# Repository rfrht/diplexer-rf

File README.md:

# Zamin ABL1000 40m Absorptive Diplexer (Rev. A)

> A high-power, 40m (7 MHz) absorptive diplexer designed to clean the output of a Zamin ABL1000 solid-state amplifier and safely dissipate destructive out-of-band harmonics.

## 📌 Project Objective
The Zamin ABL1000 utilizes four M25C24 bipolar transistors in a push-pull configuration. When driven to its absolute 600W limit, it operates deep into saturation, effectively acting as a square-wave generator rich in **odd-order harmonics** (especially the 3rd harmonic at 21 MHz). 

Standard low-pass filters reflect these harmonics back into the amplifier finals, causing extreme thermal stress and potential failure. This **absorptive diplexer** solves the problem by passing the clean 7 MHz fundamental frequency to the antenna while routing the destructive 14 MHz, 21 MHz, and 28 MHz+ harmonics into a dedicated 50-Ohm dummy load.

## 📐 Filter Topology & Specifications
* **Architecture:** 7.5 MHz Crossover, 3-Pole Butterworth Contiguous Diplexer.
* **System Impedance:** 50 Ohms constant (ensuring a flat 1.0:1 SWR presented to the amplifier across the spectrum).
* **Schematic:** [Check here](https://github.com/rfrht/diplexer-rf/blob/main/Others/lpf-40-sch.png).

### Branch Values
| Branch | Port | Component | Target Value | Actual Assembly Value |
| :--- | :--- | :--- | :--- | :--- |
| **Low-Pass** | Antenna | L1 (Series) | 1.06 µH | 1.06 µH |
| **Low-Pass** | Antenna | C1 (Shunt) | 848 pF | 840 pF |
| **Low-Pass** | Antenna | L2 (Series) | 1.06 µH | 1.06 µH |
| **High-Pass** | Dummy Load | C2 (Series) | 424 pF | 420 pF |
| **High-Pass** | Dummy Load | L3 (Shunt) | 0.53 µH | 0.53 µH |
| **High-Pass** | Dummy Load | C3 (Series) | 424 pF | 420 pF |

---

## 🛠️ Hardware & Components

### 1. Capacitor Banks (1260V Series-Parallel Matrix)
To handle 500V+ RF peaks and distribute heat, standard **Yageo 1206 630V C0G ceramic capacitors** are arranged in a 2x4 matrix (2 in series, 4 parallel rows).
* **C1 Bank (840 pF):** Three rows of 470 pF + One row of 270 pF.
* **C2 & C3 Banks (420 pF):** Three rows of 220 pF + One row of 180 pF.

### 2. High-Power Air Core Inductors
* **Material:** 12 AWG bare/enameled copper wire wound on a 1-inch (25.4 mm) form.
* **L1 & L2:** ~9 turns, spaced to ~3.6 cm in length.
* **L3:** ~6 turns, spaced to ~2.54 cm in length.
* **Orthogonal Placement:** L1 is mounted horizontally (X-axis), L2 is horizontal (Y-axis), and L3 is mounted **vertically** (Z-axis). This strict 90-degree geometry guarantees zero magnetic cross-coupling.

### 3. Ports & Dummy Load
* **Main RF Ports (Input & Antenna):** High-temperature, 2,500W-rated **RG-400 Teflon coax pigtails**, soldered directly to the board and terminating in SO-239 connectors to decouple mechanical torque from the FR4 pads.
* **Dummy Load Port:** Edge-mounted PTFE SMA connector feeding a flexible RG-316 jumper.
* **DIY Dummy Load (200W):** Two parallel Ohmite TGHD SOT-227 100-Ohm thick-film resistors (yielding a 50-Ohm load) bolted to a large heatsink with thermal paste, bridged with flat copper strap to eliminate parasitic inductance.

---

## 📏 PCB Layout & RF Design Rules

[The board](https://github.com/rfrht/diplexer-rf/blob/main/Others/lpf-40.png) is a 10x10 cm, 1 oz FR4 prototype with strict RF rules applied:

* **Trace Architecture:** The main LPF signal path uses heavy **6 mm wide traces**, mirrored identically on the top and bottom layers to act as a 2 oz equivalent.
* **Via Stitching:** Top and bottom traces are tied together using vias spaced precisely every **5 mm along the trace borders** to combat the skin effect and create a highly efficient thermal superhighway. 
* **Ground Plane:** Solid copper pours on top and bottom, featuring a 5 mm checkered/staggered via grid. Dense via clusters are placed immediately at the ground pads of C1, L3, and the coax shields. Isolation gaps are set to 3-5 mm to prevent 500V+ arc-overs.
* **Solder Mask Management:**
  * *Removed* (`tStop`/`bStop`) along the main 6 mm LPF path to allow for heavy "solder river" tinning to handle 6A+ RF peaks.
  * *Retained* on the 2 mm traces between the series SMD capacitors to act as a solder dam during assembly.
* **Magnetic Keep-Out Zones:** Ground pours are **completely removed** (`tRestrict`/`bRestrict`) underneath and extending slightly outward from L1, L2, and L3 on both layers to prevent eddy currents from destroying the inductors' Q-factor.

---

## 🔬 Assembly & Testing Strategy

1. **Component Verification:** Capacitors and inductors are verified using a 100 kHz LCR bridge (FNIRSI LC1020E) to ensure strict adherence to target values and Q-factor. L3 is tuned with its physical vertical mounting lead lengths accounted for.
2. **Finding the Amplifier "Sweet Spot":** The Zamin ABL1000 will not be pushed to a flat-topped 600W. Using an FT-991A exciter and an inline power meter on the diplexer's SMA dummy load port, the drive will be slowly increased to map the "saturation knee." The final operating point will be set just before the dummy load meter spikes, yielding a clean 200W–250W output with minimal harmonic generation.

## ⚠️ Safety Warnings
* **RF Burns:** This board operates at high RF voltages and handles massive currents. Rev A is an exposed prototype. **KEEP AWAY from the board while transmitting.** 
* **ESD Mats:** Do not test this board directly on a conductive/dissipative ESD mat, as high RF voltages can cause the mat to act as a short circuit across the bottom vias, altering stray capacitance and causing melting/fires. Elevate the board on non-conductive standoffs.

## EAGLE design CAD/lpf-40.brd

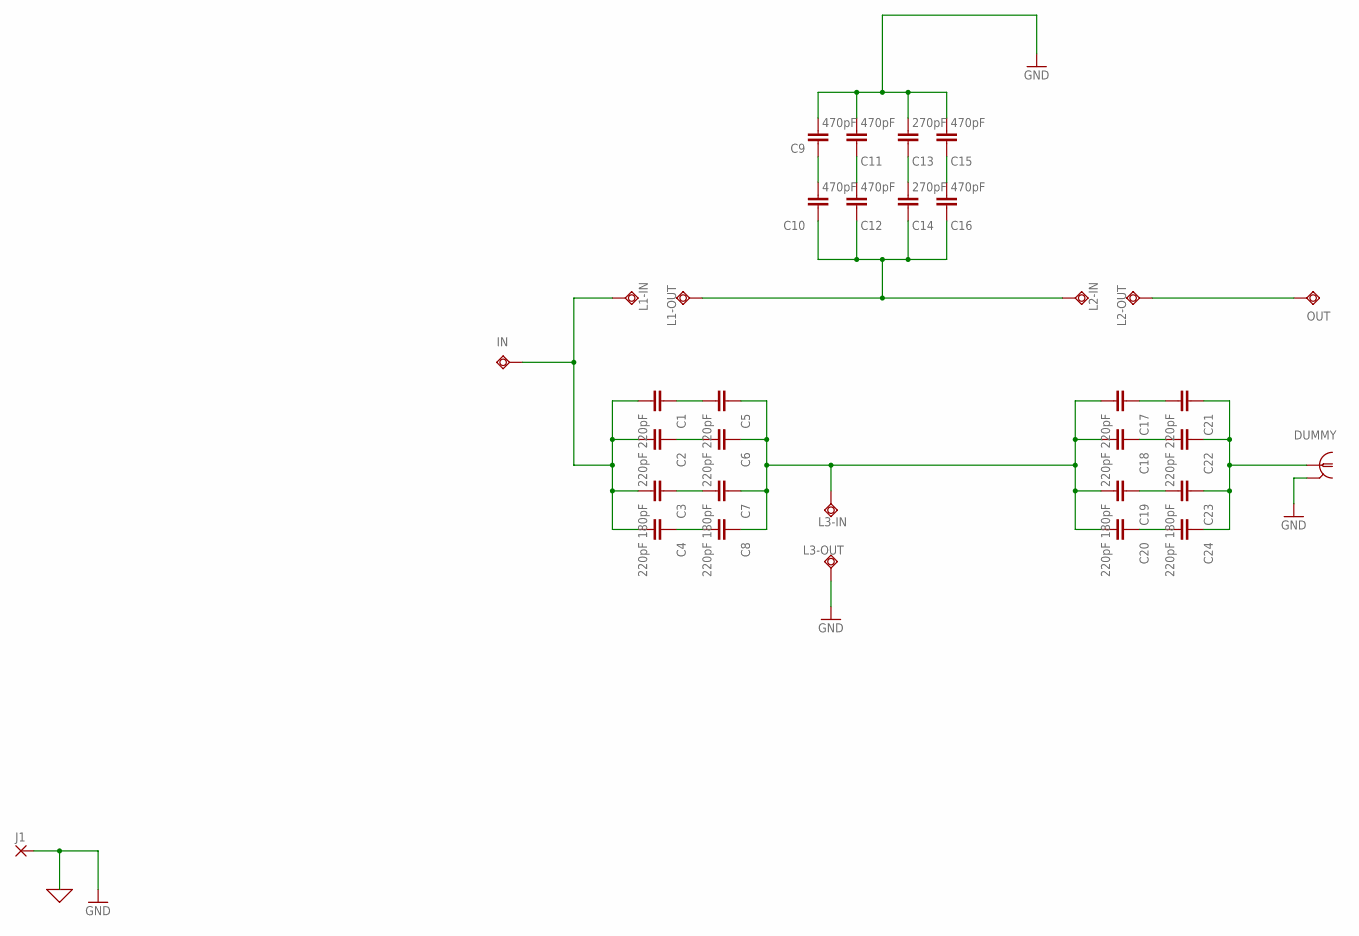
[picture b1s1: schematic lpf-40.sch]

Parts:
C1, C2, C4, C5, C6, C8, C17, C18, C20, C21, C22, C24: 220pF; 1206
C3, C7, C19, C23: 180pF; 1206
C9, C10, C11, C12, C15, C16: 470pF; 1206
C13, C14: 270pF; 1206
DUMMY: SMA-PCB; SMA-RF
IN: IN; TP11R
J1: JUMPER-1; JUMPER1
L1-IN: L1-IN; TP11R
L1-OUT, L2-IN, L2-OUT, L3-IN, L3-OUT: TPSQTP11R; TP11R
OUT: TPSQTP11R; TP11R

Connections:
DL-O: C21.1, C22.1, C23.1, C24.1, DUMMY.1
DL-P1: C5.1, C6.1, C7.1, C8.1, C17.2, C18.2, C19.2, C20.2, L3-IN.TP
GND: C9.2, C11.2, C13.2, C15.2, DUMMY.2, DUMMY.3 (2), DUMMY.4 (2), DUMMY.5 (2), J1.1, L3-OUT.TP
IN: C1.2, C2.2, C3.2, C4.2, IN.TP, L1-IN.TP
M-P1: C10.1, C12.1, C14.1, C16.1, L1-OUT.TP, L2-IN.TP
unnamed: C9.1, C10.2
unnamed: C11.1, C12.2
unnamed: C13.1, C14.2
unnamed: C15.1, C16.2
unnamed: C17.1, C21.2
unnamed: C1.1, C5.2
unnamed: C2.1, C6.2
unnamed: C3.1, C7.2
unnamed: C4.1, C8.2
unnamed: C18.1, C22.2
unnamed: C19.1, C23.2
unnamed: C20.1, C24.2
OUT: L2-OUT.TP, OUT.TP

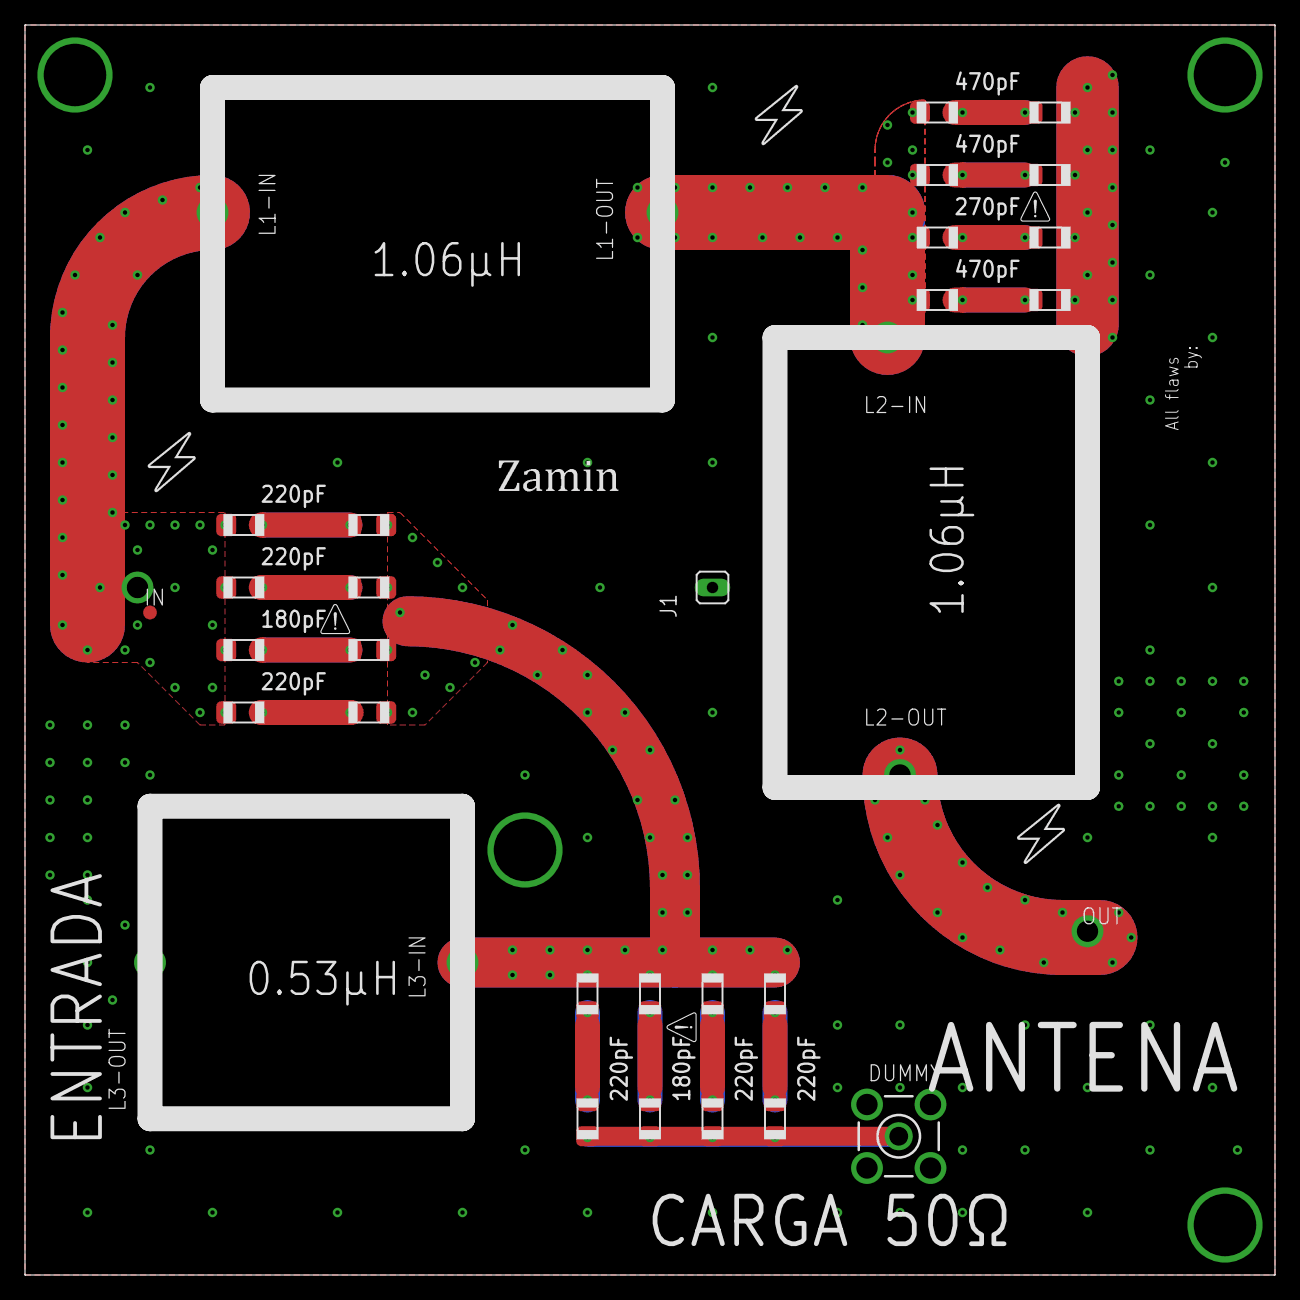
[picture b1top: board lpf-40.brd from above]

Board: 2 copper layers, 100.0 x 100.0 mm, 34 parts (0 on the bottom side), 18 nets.

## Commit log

2026-05-18 Revision A: Initial release
2026-05-18 Pequenas correções
